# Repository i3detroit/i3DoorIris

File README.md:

i3DoorIris
==========

Files for an automated iris porthole in a door

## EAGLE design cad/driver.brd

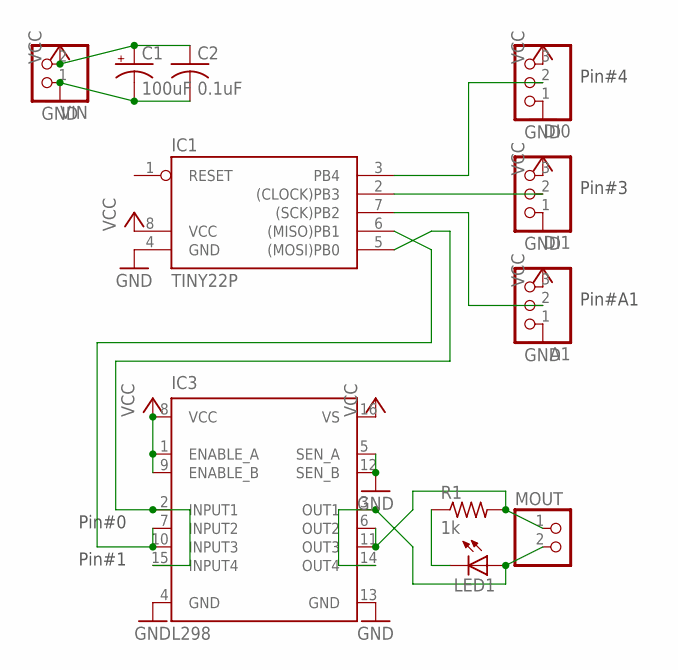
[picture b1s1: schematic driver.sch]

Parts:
A1: PINHD-1X3; 1X03
C1: 100uF; E2,5-6E
C2: 0.1uF; C025-025X050
DI0, DI1: PINHD-1X3; 1X03
IC1: TINY22P; DIL08
IC3: L298; DIL16
LED1: LED5MM
MOUT: PINHD-1X2; 1X02
R1: 1k; 0204V
VIN: PINHD-1X2; 1X02

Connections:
GND: A1.1, C1.-, C2.2, DI0.1, DI1.1, IC1.4 (GND), IC3.4 (GND), IC3.5 (SEN_A), IC3.12 (SEN_B), IC3.13 (GND), VIN.1
unnamed: IC1.5 ((MOSI)PB0), IC3.2 (INPUT1), IC3.15 (INPUT4)
unnamed: IC1.6 ((MISO)PB1), IC3.7 (INPUT2), IC3.10 (INPUT3)
unnamed: IC3.6 (OUT2), IC3.11 (OUT3), MOUT.1, R1.2
unnamed: IC3.3 (OUT1), IC3.14 (OUT4), LED1.A, MOUT.2
unnamed: LED1.K (C), R1.1
unnamed: DI1.2, IC1.2 ((CLOCK)PB3)
unnamed: DI0.2, IC1.3 (PB4)
unnamed: A1.2, IC1.7 ((SCK)PB2)
VCC: A1.3, C1.+, C2.1, DI0.3, DI1.3, IC1.8 (VCC), IC3.1 (ENABLE_A), IC3.8 (VCC), IC3.9 (ENABLE_B), IC3.16 (VS), VIN.2

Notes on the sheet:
Pin#4
Pin#3
Pin#A1
Pin#0
Pin#1

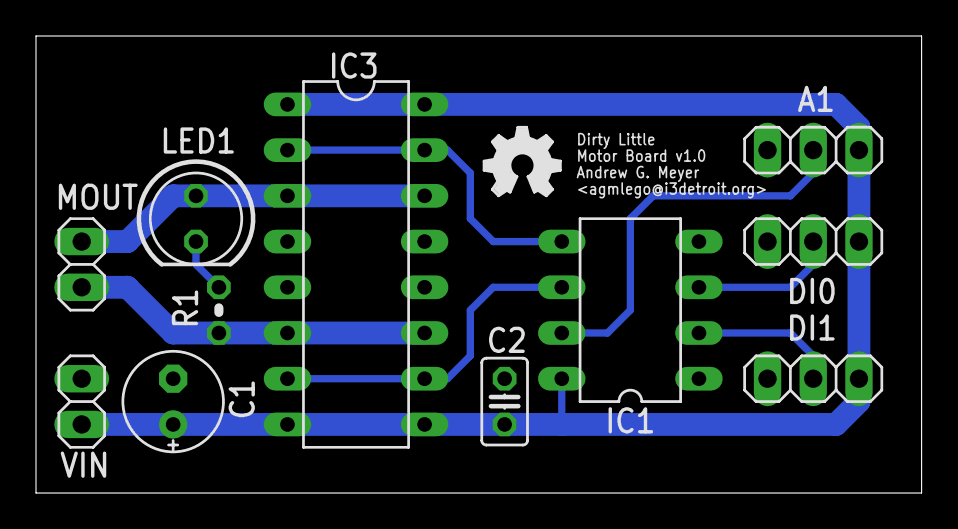
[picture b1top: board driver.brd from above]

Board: 2 copper layers, 49.2 x 25.4 mm, 12 parts (0 on the bottom side), 10 nets.

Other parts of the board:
U$1: OSHW_FILLX150_NOTEXT

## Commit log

2014-04-10 Initial draft, mostly-working code for the wrong current sensor.
2014-08-15 Backup commit before wiping machine
